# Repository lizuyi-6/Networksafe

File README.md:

# AetherGuard

AetherGuard is a server security platform with a control plane, distributed host agents, a Rust fastpath sidecar, and hardware-backed safety gates for dangerous operations.

Product claim: **AetherGuard 完全最后防线**. Engineering definition: Final Defense Mode is a detectable, auditable, fail-closed mode where the control plane can request and audit dangerous actions, but the final grant is enforced by hardware. The root-resistant variant moves that final network release decision outside the protected server into the self-developed **AetherGuard Root-Resistant Gateway Appliance** — an industrial multi-port gateway appliance integrating an independent security authorization controller, Secure Element / TPM, and hardware-level fail-closed interlock.

## Quick Start

One-shot setup — generates `.env` (Docker) and `backend/.env` (local dev) from the `.env.example` templates with cryptographically random secrets. Existing files are never overwritten:

```bash
node scripts/setup.mjs              # add --install to also npm-install backend/ + frontend/
                                    # bash-only alternative: bash deployment/production/setup-env.sh
```

Docker, all services (requires Docker Compose v2.24+; the legacy `docker-compose` v1 binary cannot parse this compose file):

```bash
node scripts/setup.mjs
docker compose up -d --build

# Console + API proxy: http://127.0.0.1:8080
# Backend/Redis/Postgres/MinIO are internal-only in production Compose.
# Login: ADMIN_EMAIL / ADMIN_PASSWORD from .env — setup prints the generated password once
```

Fresh Linux host, one command (installs Docker if missing, generates `.env`, builds and starts, waits for backend health):

```bash
sudo bash scripts/install.sh
```

Air-gapped customer host (no internet, optionally no preinstalled Docker): build a self-contained bundle on a connected machine, transfer it, install fully offline — details in `deployment/offline/README.md`:

```bash
node scripts/release/build-offline-bundle.mjs --include-docker    # online build machine
# transfer dist/offline/aetherguard-offline-<ver>-<arch>.tar.gz to the customer host, then:
tar -xzf aetherguard-offline-*.tar.gz -C /opt/aetherguard
cd /opt/aetherguard && sudo bash install.sh
```

Local development — the backend refuses to start without `JWT_SECRET` and `AUDIT_LOG_SECRET`, so create `backend/.env` first (the setup script writes it with dev-safe defaults, including `DISABLE_REDIS=true`, which is dev-only and rejected in production):

```bash
node scripts/setup.mjs

cd backend
npm install
npm run dev

cd frontend
npm install
npm run dev
```

Optional components: `simulator/` and `e2e/` are separate npm packages (`node scripts/setup.mjs --all` installs them too); `rust-fastpath/` needs Rust 1.85 (`cargo build --release`); firmware host-side tests need gcc (`make -f test/Makefile test` from `firmware/controller-stm32h5/`).

Release-relevant checks:

```bash
cd backend && npm run typecheck
cd frontend && npm run typecheck
node scripts/guards/check-route-db-access.mjs
node scripts/guards/check-no-direct-api-fetch.mjs
```

## Current Software Validation

The latest software-only local validation is recorded in:

- `docs/reports/software-validation-status-2026-07-27.md`
- `docs/reports/software-validation-status-2026-07-27.json`
- `backend/test-data/dataset-eval-report.json`

Current evidence on the tested x86_64 Linux host:

- Backend: 248 Jest suites and 3,291 tests passed. Coverage is 65.90% statements, 51.41% branches, 65.90% functions, and 66.21% lines. Tests ran with Redis disabled and do not substitute for live external-service integration.
- Synthetic dataset: 4,500 samples produced 63.97% attack detection and 0% false positives on the 1,200 tracked synthetic normal samples. These are corpus results, not production detection or FPR claims.
- Rust fastpath: tests, Clippy, and release build passed. The latest fixed-key loopback reproduction measured 56.6k–61.6k QPS across three rounds, with a short concurrency-sweep peak of 75.1k QPS and no request errors. A stable 100k QPS result was not reproduced in this run.
- Chromium release subset: all 10 runnable tests passed, and 1 pitch-enabled-only test was skipped. This covers the local Chromium release subset only, not every E2E file, browser, operating system, or production deployment.
- Rescue and gateway simulator fail-closed checks passed as software tests only; they do not validate physical hardware.
- Local AI latency, live PostgreSQL/Redis/S3/IdP/notification integrations, ARM64/cross-OS support, agent resource targets, and production network capacity remain unvalidated in this environment.

The historical March 2026 Docker report remains useful as a dated snapshot, but it is not the source of truth for current software performance or dataset claims.

Focused Final Defense checks:

```bash
cd backend
npx jest src/__tests__/services/final-defense.service.test.ts
npx jest src/__tests__/services/hardware-authorization.service.test.ts
npx jest src/__tests__/services/deployment-run.service.test.ts
npx jest src/__tests__/services/device-control.service.test.ts
npx jest src/__tests__/companion/serial-device-companion.test.ts
```

## Architecture

```mermaid
flowchart LR
    User["Operator / API Client"] --> Frontend["React Console"]
    Frontend --> Backend["Node.js Control Plane"]
    Backend --> DB["SQLite / PostgreSQL"]
    Backend --> Redis["Redis"]
    Backend --> Agent["Host Agent"]
    Agent --> Fastpath["Rust Fastpath"]
    Agent --> Companion["Local Companion"]
    Companion --> Board["Gateway Appliance Controller"]
    Board --> Interlock["Hardware Fail-closed Interlock"]
    Agent --> ServerNIC["Server Network Ports"]
    ServerNIC --> NIGW["Gateway Appliance (L2 Bridge)"]
    NIGW --> Network["LAN / WAN"]
    NIGW --> Mgmt["Independent MGMT / Cellular"]
```

Primary components:

| Path | Purpose |
| --- | --- |
| `backend/` | Express API, Socket.IO gateways, services, repositories, companion logic, tests |
| `frontend/` | React console, typed API client, pages, demo data |
| `rust-fastpath/` | High-throughput traffic processing sidecar |
| `e2e/` | Playwright release and UI verification |
| `deployment/` | Production helper scripts and deploy bundles |
| `hardware/aetherguard-network-isolation-gateway-v1/` | AetherGuard Root-Resistant Gateway Appliance hardware baseline (active primary hardware) |
| `hardware/factory/aetherguard-serial-deployer-ev1/` | Archived — legacy serial deployer factory package |
| `hardware/kicad/esp32-serial-deployer-pcb/` | Archived — KiCad source for the legacy serial deployer PCB |
| `docs/` | Architecture, product, readiness, and archive index documents |

## Final Defense Mode

Final Defense Mode treats the backend, database, and API request as potentially untrusted for high-risk actions.

High-risk actions such as `host_remove`, `wipe_data`, `factory_reset`, `recovery_flash`, and `critical_config_change` must satisfy all of the following:

- The local companion reads a signed local policy from `/etc/aetherguard/final-defense-policy.json`.
- The requested action, target, script path, release window, and interlock target are in the local policy allow-list.
- The hardware grant signature verifies against the provisioned hardware public key.
- The grant message includes and matches `policyDigest`, `challenge`, `breakerTarget`, `interlockAction`, payload hash, expiry, and monotonic counter.
- Interlock feedback is healthy and matches the expected state.

Interlock states are normalized as:

```ts
type InterlockState = 'isolated' | 'armed' | 'released' | 'fault' | 'disabled' | 'unknown';
```

Legacy `asserted` is mapped to `isolated`.

Failure behavior is closed by default: signature failure, counter rollback, policy digest mismatch, expired grant, missing external DC, feedback mismatch, board disconnect, or heartbeat loss keeps or returns the management link to `isolated`.

The external product statement is conditional. “完全最后防线” is only valid when the management link is actually wired through the interlock, Final Defense Mode is enabled, the local policy is signed, the secure element is provisioned, and companion plus board health are confirmed. v1 controls the low-voltage network or management link only; it does not switch mains power or directly cut production host power.

## Root-Resistant Final Defense

> **Evidence status (2026-08 security audit): EXPERIMENTAL.** The canonical
> `deployment/gateway` data plane has not passed Linux namespace/L2-bridge
> integration gates, systemd-VM gates, or hardware-in-the-loop campaigns.
> Gateway status is a three-level evidence model — `reported` (self-report),
> `verified` (reserved: signed control-channel verification), `attested`
> (reserved: server-verified hardware attestation quote). Only `attested`
> can drive "Root-Resistant Active"; the attestation verifier is **not yet
> implemented**, so high-risk root-resistant actions stay fail-closed and
> self-reported fields can never restore `active`. See
> `docs/security-audit/2026-08-remediation-matrix.md`.

Root-resistant mode assumes the protected server OS, local agent, local companion, scripts, and host logs may be fully controlled by an attacker with root. In that threat model, the trusted boundary is no longer the host companion. It is the **AetherGuard Root-Resistant Gateway Appliance**:

- Dual 1GbE RJ45 transparent L2 bridge with `SERVER`, `LAN/WAN`, and independent `MGMT` ports; cellular is an optional management path.
- The `SERVER` to `LAN/WAN` bridge is fail-closed. `isolated` blocks protected server forwarding while preserving the gateway's own management channel.
- The appliance holds signed policy state, hardware identity, firmware measurement, and secure-element backed release grants outside the protected server.
- Strong “root-resistant active” status requires the appliance present, policy digest match, firmware digest plus attestation, secure element, both data ports linked, independent management path, and a healthy `armed` or `isolated` bridge state.
- The claim only covers network links physically cabled through the appliance. Out-of-band BMC, Wi-Fi, spare NICs, local console, direct storage damage, and host disk encryption by root are outside v1 protection unless separately controlled.

## Hardware Shapes

| Hardware | Status | Role |
| --- | --- | --- |
| AetherGuard Root-Resistant Gateway Appliance | **Active — primary hardware** | Self-developed industrial multi-port gateway appliance: dual 1GbE transparent L2 bridge (SERVER, LAN/WAN) + independent MGMT port, STM32H5/U5 security authorization controller, Secure Element / TPM (OPTIGA Trust M / SE050 / ATECC608B), hardware-level fail-closed interlock with feedback verification. Controls protected server network release outside the host. |
| Legacy ESP32 serial deployment dongle | Archived (superseded) | Former physical confirmation device for local deployment/removal over USB-TTL serial. Replaced by Gateway Appliance. |
| Legacy Control Board v1 | Archived (superseded) | Former ESP32-S3 + ATECC608C control board for hardware grants. Replaced by Gateway Appliance Controller. |

Gateway Appliance controller protocol is newline-delimited JSON:

- Companion to controller: `hello`, `command physical_confirmation_required`, `command interlock_assert`, `command interlock_release`
- Controller to companion: `state`, `heartbeat`, `alert`, `physical_confirmation_ack`, `interlock_result`

The legacy ESP32 deployment dongle protocol (`AG:REQ:*` allow-list) is archived and no longer active.

## API Surface

Final Defense API routes:

- `GET /api/final-defense/status`
- `POST /api/final-defense/policies`
- `POST /api/final-defense/actions`
- `POST /api/final-defense/gateways/status/report`
- `POST /api/final-defense/gateways/actions`

Route handlers must use `sendSuccess()` and `sendError()` from `backend/src/core/http/api-response.ts`. Route files under `backend/src/api/routes/` must not access the database directly; use services or repositories.

Frontend API calls must go through `frontend/src/services/api.ts`.

## Validation Status

Validated in the current production baseline:

- Backend and frontend typechecks for the Final Defense implementation.
- Route DB access guard.
- Frontend direct API fetch guard.
- Focused Jest coverage for hardware grant signing, Final Defense service policy checks, companion denial of untrusted scripts, deployment run, and device control paths.
- UI status model for root-resistant “Final Defense Active” only when an external AetherGuard Root-Resistant Gateway Appliance reports secure element, matching policy digest, firmware attestation, linked data ports, independent management path, and healthy bridge state. As of the 2026-08 audit this status additionally requires the server-side `attested` verification level, which is not yet reachable — see the Root-Resistant evidence-status note above.

Not yet validated in this workspace:

- Real Gateway Appliance hardware-in-the-loop release and feedback test.
- Secure element provisioning ceremony on physical OPTIGA Trust M / ATECC608B.
- Real Gateway Appliance hardware-in-the-loop bridge isolation and release test.
- Secure boot / measured boot chain for physical gateway firmware.

## Production Rules

- Do not call `ensureSchema()` in request handlers or WebSocket processors. Prepare service-owned tables in `backend/src/bootstrap/persistence.ts`.
- `DB_MODE=postgres` is required for production.
- `DISABLE_REDIS` must not be enabled in production.
- Do not commit generated outputs, KiCad scratch trees, router exchange files, probe reports, or generated PPTX decks.
- Demo and pitch-only frontend routes such as `/aetherguard-deck` are disabled by default. Set `VITE_ENABLE_PITCH_ROUTES=true` only for local demo builds.

## Artifact Archive

Large generated artifacts and hardware experiment intermediates were moved out of the repository to:

```text
X:\repos\Networksafe-archive\20260513-pre-cleanup
```

See `docs/artifact-archive-index.md` for the archive categories and file-level manifest location.

## License

MIT. See `LICENSE`.

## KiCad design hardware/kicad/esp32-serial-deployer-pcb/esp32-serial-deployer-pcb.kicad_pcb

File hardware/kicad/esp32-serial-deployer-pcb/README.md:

# ESP32 Serial Deployer PCB v1

This directory contains the first single-board KiCad project for the ESP32 serial deployer.

## Scope

- Board size: `100 mm x 72 mm`
- Stack-up: `4-layer`, `1.6 mm FR-4`
- Mounting: `4 x M2` holes, `3.5 mm` inset from each edge
- Architecture:
  - `ESP32-WROOM-32E`
  - `CP2102N` service/debug bridge on rear `USB-C`
  - `CP2102N` host bridge on right-side `USB-A` pigtail pads
  - Dual `VBUS` inputs ORed into `5V_SYS`
  - `AP2112K-3.3` main regulator
  - On-board OLED header, three UI buttons, RGB LED, buzzer driver, BOOT/RESET, test points

## Files

- `esp32-serial-deployer-pcb.kicad_pro`
- `esp32-serial-deployer-pcb.kicad_sch`
- `esp32-serial-deployer-pcb.kicad_pcb`
- `esp32-serial-deployer-pcb.kicad_sym`
- `esp32-serial-deployer-pcb.pretty/`
- `fp-lib-table`
- `sym-lib-table`
- `reports/`
- `tools/generate_pcb_v1.py`
- `tools/repair_pcb_connectivity.py`

## Source Of Truth

- The KiCad project files in this directory are the active design source.
- `tools/generate_pcb_v1.py` is now a reference/base-board generator used to keep symbol, footprint, and net assignments synchronized.
- Recovery experiments live in `scratch/` and are not the fabrication source of truth.

## Interface Baseline

- OLED: `GPIO21` / `GPIO22`
- Buttons: `GPIO18` / `GPIO19` / `GPIO23`
- RGB: `GPIO25` / `GPIO26` / `GPIO27`
- Buzzer driver: `GPIO14`
- Host deployment UART: `GPIO16` / `GPIO17`
- Service/debug UART: `GPIO1` / `GPIO3`

## Power Strategy

- `USB-C VBUS -> PTC fuse -> Schottky OR -> 5V_SYS`
- `Host pigtail VBUS -> PTC fuse -> Schottky OR -> 5V_SYS`
- `5V_SYS -> AP2112K-3.3 -> 3V3`
- Both `CP2102N` bridges are modeled as `3V3`-powered devices with their respective USB `VBUS` pins sensed through divider networks.

## USB Split

- Rear `USB-C`: flashing, debug console, service power input
- Right-side `USB-A` pigtail: target-host deployment bridge only
- The two USB data paths are electrically separate

## BOM Direction

Use JLC/LCSC-friendly packages wherever possible:

- QFN-24 `CP2102N`
- `ESP32-WROOM-32E`
- `AP2112K-3.3` in `SOT-23-5`
- `0603` passives
- `SOD-123` Schottky diodes
- Small `SOT-23` NPNs for auto-download and buzzer drive

## KiCad 9 Status

The project now loads in `KiCad 9.0.7` CLI:

- `kicad-cli sch export netlist` succeeds
- `kicad-cli sch erc` runs and writes `reports/erc.rpt`
- `kicad-cli pcb drc` runs and writes `reports/drc.rpt`
- `kicad-cli pcb drc --schematic-parity` runs and writes `reports/parity.rpt`

Current validation is not yet clean and the board is not fabrication-ready:

- ERC: currently high-noise and still requires schematic cleanup
- PCB DRC: stable board baseline is down to `3` DRC violations plus `39` unconnected items
- The remaining PCB issues are concentrated in explicit ground/power closure, not broad project load failures
- Schematic parity still needs cleanup after the exposed-pad and ground-net corrections

This means the project is a KiCad 9 native, editable recovery baseline, but it is not ready for fabrication yet. The remaining work is board-quality cleanup:

- finish the remaining ground and power routing closure
- clean up ERC and schematic-parity drift introduced during recovery
- verify footprint drill sizes and custom footprints against final purchased parts
- re-run DRC/DRC parity after the next routing pass

## Firmware Profile

Use the new PlatformIO environment `serial_deployer_pcb_v1` for the PCB variant. It keeps the same GPIO map and switches `BUZZER_ACTIVE_LEVEL` to `HIGH`.

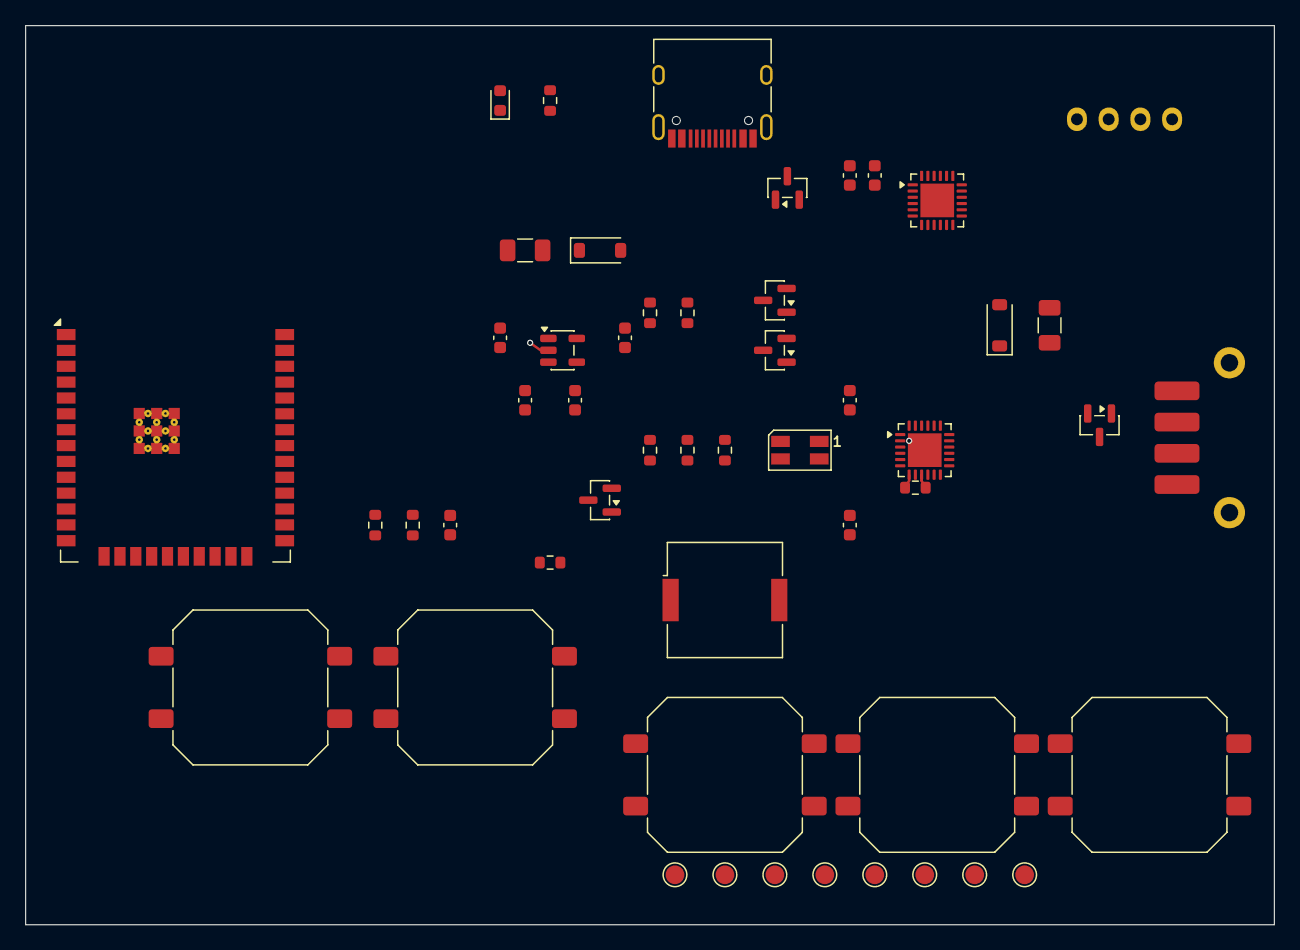
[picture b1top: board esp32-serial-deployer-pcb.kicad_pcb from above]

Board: 4 copper layers, 100.0 x 72.0 mm, 51 parts (0 on the bottom side), 37 nets.

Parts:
BZ1: Buzzer; Buzzer_Murata_PKMCS0909E
C1, C2, C9: 10u; C_0603_1608Metric
C3: 1u; C_0603_1608Metric
C4, C6, C8: 0.1u; C_0603_1608Metric
C5, C7: 4.7u; C_0603_1608Metric
D1, D2: B5819W; D_SOD-123
D3: PWR LED; LED_0603_1608Metric
D10: RGB LED; LED_RGB_Wuerth-PLCC4_3.2x2.8mm_150141M173100
F1, F2: PTC500mA; Fuse_1206_3216Metric
J1: Service USB-C; USB_C_Receptacle_HRO_TYPE-C-31-M-12
J2: USB-A Pigtail; USB_A_Pigtail_Pads_1x4_Edge
J3: OLED 0.96in I2C; OLED_096_I2C_Module_1x4
Q1, Q2, Q3: MMBT3904; SOT-23
R1, R2: 5.1k; R_0603_1608Metric
R3, R4: 10k; R_0603_1608Metric
R13, R14, R15: 330; R_0603_1608Metric
R16, R18: 1k; R_0603_1608Metric
R17: 4.7k; R_0603_1608Metric
SW1: BOOT; SW_Push_1P1T_NO_CK_PTS125Sx43SMTR
SW2: RESET; SW_Push_1P1T_NO_CK_PTS125Sx43SMTR
SW3: OK; SW_Push_1P1T_NO_CK_PTS125Sx43SMTR
SW4: NEXT; SW_Push_1P1T_NO_CK_PTS125Sx43SMTR
SW5: BACK; SW_Push_1P1T_NO_CK_PTS125Sx43SMTR
TP1: 3V3; TestPoint_Pad_D1.5mm
TP2: GND; TestPoint_Pad_D1.5mm
TP3: EN; TestPoint_Pad_D1.5mm
TP4: IO0; TestPoint_Pad_D1.5mm
TP5: TX0; TestPoint_Pad_D1.5mm
TP6: RX0; TestPoint_Pad_D1.5mm
TP7: TX2; TestPoint_Pad_D1.5mm
TP8: RX2; TestPoint_Pad_D1.5mm
U1: ESP32-WROOM-32E
U2: CP2102N Service; QFN-24-1EP_4x4mm_P0.5mm_EP2.7x2.7mm
U3: CP2102N Host; QFN-24-1EP_4x4mm_P0.5mm_EP2.7x2.7mm
U4: AP2112K-3.3; SOT-23-5
U5, U6: USB ESD; SOT-23

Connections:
3V3: BZ1.1, C2.1, C4.1, C5.1, C6.1, C7.1, C8.1, C9.1, J3.1, R3.1, R4.1, R16.1, R18.1, TP1.1, U1.2, U2.5, U2.6, U2.7, U2.9, U3.5, U3.6, U3.7, U4.5
5V_SYS: C1.1, D1.2, D2.2, U4.1, U4.3
BTN_BACK: SW5.1, U1.37
BTN_NEXT: SW4.1, U1.31
BTN_OK: SW3.1, U1.30
BUZZER_CTRL: R17.1, U1.13
BUZZER_CTRL_DRV: Q3.1, R17.2
BUZZER_SW: BZ1.2, Q3.3
ESP_EN: C3.1, Q1.3, R3.2, SW2.1, TP3.1, U1.3
ESP_IO0: Q2.3, R4.2, SW1.1, TP4.1, U1.25
GND: C1.2, C2.2, C3.2, C4.2, C5.2, C6.2, C7.2, C8.2, C9.2, D3.1, D10.2, J1.A1, J1.A12, J1.B1, J1.B12, J1.S1, J2.4, J3.2, Q1.2, Q2.2, Q3.2, R1.2, R2.2, SW1.2, SW2.2, SW3.2, SW4.2, SW5.2, TP2.1, U1.1, U1.39, U2.2, U2.25, U3.2, U3.25, U4.2, U5.2, U6.2
HOST_CP2102_RST_N: R18.2, U3.9
HOST_DN: J2.2, U3.4, U6.3
HOST_DP: J2.3, U3.3, U6.1
LED_B: D10.4, R15.1
LED_B_DRV: R15.2, U1.12
LED_G: D10.3, R14.1
LED_G_DRV: R14.2, U1.11
LED_R: D10.1, R13.1
LED_R_DRV: R13.2, U1.10
OLED_SCL: J3.3, U1.36
OLED_SDA: J3.4, U1.33
PWR_LED_N: D3.2, R16.2
UART0_RX: TP6.1, U1.34, U2.20
UART0_TX: TP5.1, U1.35, U2.21
UART2_RX: TP8.1, U1.27, U3.20
UART2_TX: TP7.1, U1.28, U3.21
USB_CC1: J1.A5, R1.1
USB_CC2: J1.B5, R2.1
USB_C_DN: J1.A7, J1.B7, U2.4, U5.3
USB_C_DP: J1.A6, J1.B6, U2.3, U5.1
USB_DTR: Q2.1, U2.23
USB_RTS: Q1.1, U2.19
VBUS_HOST_PROT: D2.1, F2.2
VBUS_HOST_RAW: F2.1, J2.1, U3.8
VBUS_USB_C_PROT: D1.1, F1.2
VBUS_USB_C_RAW: F1.1, J1.A4, J1.A9, J1.B4, J1.B9, U2.8

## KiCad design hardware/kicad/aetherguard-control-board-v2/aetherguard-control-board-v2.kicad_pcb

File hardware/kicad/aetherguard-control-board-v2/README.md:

# AetherGuard Control Board v2 KiCad Project

Single-host physical authorization board with RTC, SD card audit logging, and Wi-Fi/BLE.

## Changes from v1

- Added PCF8563 RTC with CR1220 battery backup (I2C 0x51, shared bus)
- Added Micro-SD card slot (SPI mode, GPIO1/2/3/6)
- Expanded ESP32-S3 symbol to expose GPIO1-3, 6-7
- Added 2x 47uF bulk capacitors on 3.3V rail for peak current headroom
- Wi-Fi/BLE enabled (ESP32-S3 PCB antenna, keepout zone preserved)

## Board Specs

- 90mm x 60mm, 4-layer FR-4, 1.6mm
- ENIG surface finish, black solder mask
- JLCPCB SMT compatible (0603 passives, LCSC parts)

## Schematic Hierarchy (5 sheets)

1. `sheets/power-input.kicad_sch` — USB-C, ESD, TPS2121, LMR16006, AP2112K
2. `sheets/mcu-usb-secure.kicad_sch` — ESP32-S3, ATECC608C, USB, UART
3. `sheets/ui-panel.kicad_sch` — OLED, RGB LED, buttons, buzzer
4. `sheets/isolated-io.kicad_sch` — Optocoupler interlock I/O
5. `sheets/rtc-storage.kicad_sch` — PCF8563 RTC + CR1220 + Micro-SD

## Key Components

| Ref | Part | Package | LCSC | Function |
|-----|------|---------|------|----------|
| U1 | ESP32-S3-WROOM-1-N8R2 | Module | — | Main MCU |
| U2 | ATECC608C-SSHDA-T | SOIC-8 | C649795 | Secure element |
| U3 | LMR16006YDDCR | SOT-23-6 | C477878 | 12/24V→5V buck |
| U4 | AP2112K-3.3TRG1 | SOT-23-5 | C51118 | 5V→3.3V LDO |
| U5 | TPS2121DRLR | DHWQFN-14 | C477879 | Power OR-ing |
| U7,U8 | VOS617A | SO-4 | C131455 | Optocouplers |
| U9 | PCF8563T/5 | SOIC-8 | C7488 | RTC |
| BT1 | CR1220 holder | SMD | C70377 | RTC battery |
| J1 | USB4110-GF-A | USB-C | — | USB connector |
| J6 | TF-115 | SMD | C393941 | Micro-SD slot |

## GPIO Assignment

| GPIO | Function | Sheet |
|------|----------|-------|
| 0 | BOOT | mcu-usb-secure |
| 1 | SD_MOSI | rtc-storage |
| 2 | SD_MISO | rtc-storage |
| 3 | SD_SCK | rtc-storage |
| 4 | Cancel button | ui-panel |
| 5 | Confirm button | ui-panel |
| 6 | SD_CS | rtc-storage |
| 7 | RTC_INT# | rtc-storage |
| 8 | I2C SDA | mcu-usb-secure |
| 9 | I2C SCL | mcu-usb-secure |
| 10 | ATECC wake | mcu-usb-secure |
| 11 | RGB LED R | ui-panel |
| 12 | RGB LED G | ui-panel |
| 13 | RGB LED B | ui-panel |
| 14 | Buzzer PWM | ui-panel |
| 15 | Interlock OUT | isolated-io |
| 16 | Interlock FB | isolated-io |
| 17 | UART TX | mcu-usb-secure |
| 18 | UART RX | mcu-usb-secure |
| 19 | USB D- | mcu-usb-secure |
| 20 | USB D+ | mcu-usb-secure |
| 21 | Ext power sense | power-input |

## Layer Stack

| Layer | Function |
|-------|----------|
| F.Cu | Signal + components |
| In1.Cu | Solid GND plane |
| In2.Cu | Power (5V/3.3V split) + signal |
| B.Cu | Signal + components |

## Validation

```powershell
$cli = 'C:\Program Files\KiCad\9.0\bin\kicad-cli.exe'
$tmp = Join-Path $env:TEMP 'ag-v2-test'
New-Item -ItemType Directory -Force -Path $tmp | Out-Null

& $cli sch erc hardware/kicad/aetherguard-control-board-v2/aetherguard-control-board-v2.kicad_sch --output "$tmp\erc.rpt"
& $cli pcb drc hardware/kicad/aetherguard-control-board-v2/aetherguard-control-board-v2.kicad_pcb --output "$tmp\drc.rpt"
```

## Manufacturing Target

JLCPCB 4-layer prototype:
- FR-4, 1.6mm, 1oz copper
- ENIG or HASL lead-free
- Black solder mask, white silkscreen
- Min trace/space: 0.15mm
- Signal via: 0.3/0.6mm drill/pad
- Power via: 0.5/1.0mm drill/pad

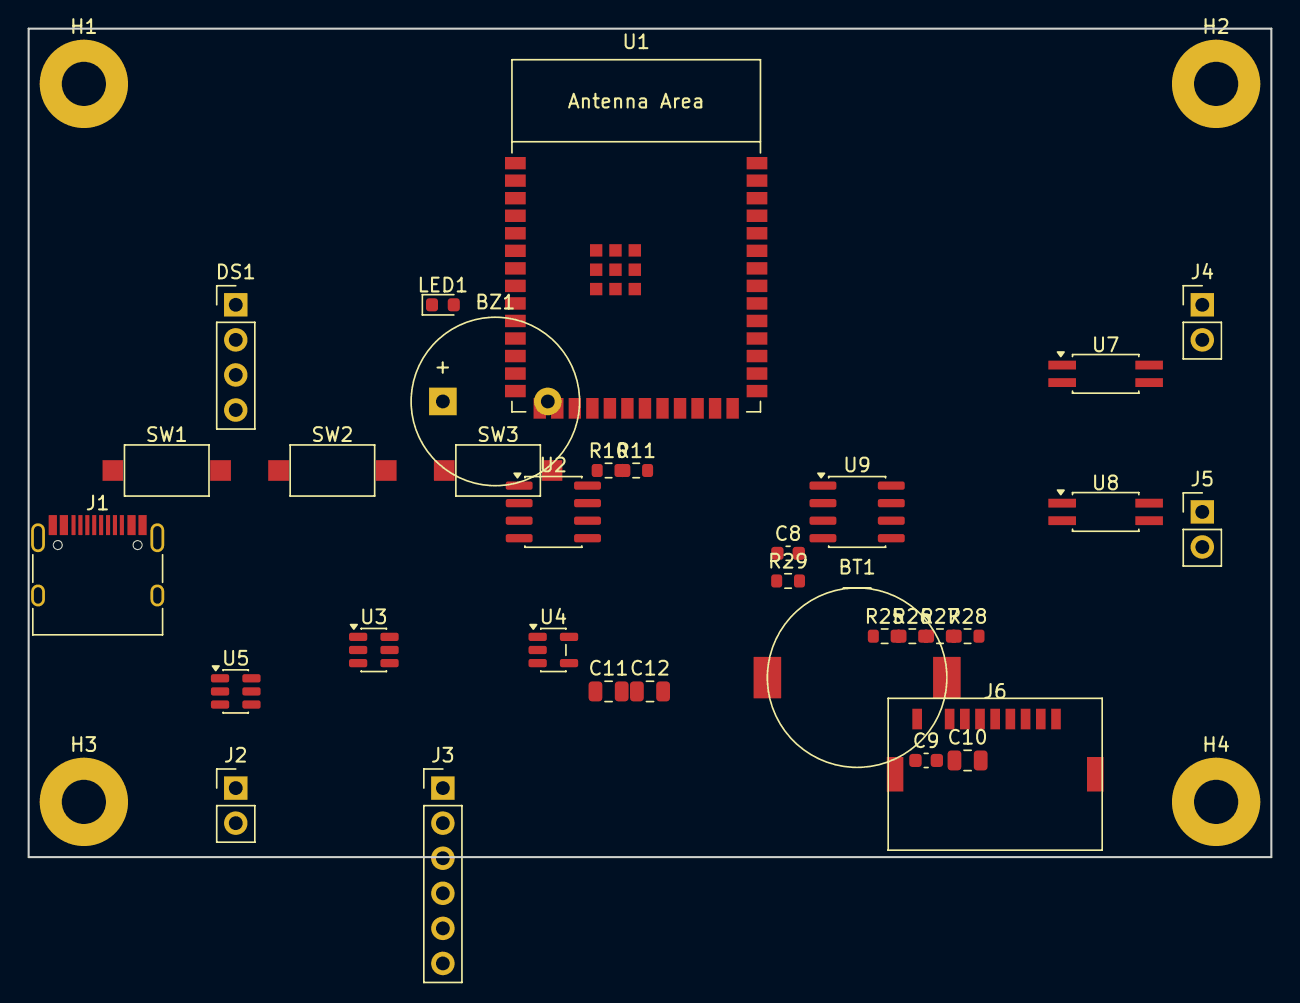
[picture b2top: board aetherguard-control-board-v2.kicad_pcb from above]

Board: 4 copper layers, 90.0 x 60.0 mm, 37 parts (0 on the bottom side), 5 nets, no tracks yet.

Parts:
BT1: CR1220; AetherGuard_CR1220_Holder
BZ1: Buzzer_12x9.5RM7.6
C8, C9: C_0603_1608Metric
C10, C11, C12: C_0805_2012Metric
DS1: PinHeader_1x04_P2.54mm_Vertical
H1, H2, H3, H4: MountingHole_3.2mm_M3_Pad
J1: AetherGuard_USB4110_GFA
J2, J4, J5: PinHeader_1x02_P2.54mm_Vertical
J3: PinHeader_1x06_P2.54mm_Vertical
J6: Micro_SD; AetherGuard_MicroSD_Push_Push
LED1: LED_0603_1608Metric
R10, R11, R25, R26, R27, R28, R29: R_0603_1608Metric
SW1, SW2, SW3: SW_SPST_CK_RS282G05A3
U1: AetherGuard_ESP32-S3-WROOM-1
U2, U9: SOIC-8_3.9x4.9mm_P1.27mm
U3, U5: SOT-23-6
U4: SOT-23-5
U7, U8: SO-4_4.4x2.3mm_P1.27mm

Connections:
5V_SYS: U4.1, U5.2
+3V3: BT1.1, C8.1, C9.1, C10.1, C11.1, C12.1, DS1.2, R10.1, R11.1, R25.1, R26.1, R27.1, R28.1, R29.1, U2.8, U4.5, U9.8
GND: BT1.2, C8.2, C9.2, C10.2, C11.2, C12.2, DS1.1, H1.1, H2.1, H3.1, H4.1, J2.2, U2.4, U3.5, U4.2, U5.5, U7.3, U8.3, U9.4
I2C_SCL: DS1.3, R11.2, U2.6, U9.6
I2C_SDA: DS1.4, R10.2, U2.5, U9.5

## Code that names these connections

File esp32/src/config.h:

/**
 * AetherGuard ESP32 serial deployer configuration.
 *
 * Default baseline:
 * - Jumper prototype on an ESP32 development board
 * - 0.96" I2C OLED
 * - Three buttons wired to GND with INPUT_PULLUP
 * - Common-cathode RGB module
 * - Active-low buzzer module
 * - One external CP2102 used in deployment mode on UART2
 *
 * Optional board profile:
 * - AG_HW_PROFILE_PCB_V1=1 for the single-board KiCad PCB variant
 * - Keeps the same GPIO map, but flips the buzzer control polarity to HIGH
 */

#ifndef CONFIG_H
#define CONFIG_H

#include <Arduino.h>

// Feature flags
#ifndef ENABLE_ENCRYPTION
#define ENABLE_ENCRYPTION       0
#endif

#ifndef ENABLE_EXPERIMENTAL_CLOUD
#define ENABLE_EXPERIMENTAL_CLOUD 0
#endif

#ifndef AG_HW_PROFILE_PCB_V1
#define AG_HW_PROFILE_PCB_V1     0
#endif

// 1. I2C OLED (SSD1306)
#define ENABLE_SCREEN           1
#define SCREEN_WIDTH            128
#define SCREEN_HEIGHT           64
#define SCREEN_ADDRESS          0x3C
#define DISPLAY_I2C_CLOCK_HZ    400000
#define PIN_I2C_SDA             21
#define PIN_I2C_SCL             22

// 2. Buttons
// Use non-strap GPIOs so a held button does not disturb boot.
#define PIN_BTN_OK              18
#define PIN_BTN_NEXT            19
#define PIN_BTN_BACK            23

// 3. RGB module
#define PIN_RGB_RED             25
#define PIN_RGB_GREEN           26
#define PIN_RGB_BLUE            27
#define RGB_COMMON_ANODE        0

// 4. Buzzer module
#define PIN_BUZZER              14
#define BUZZER_ACTIVE           1
#if AG_HW_PROFILE_PCB_V1
#define BUZZER_ACTIVE_LEVEL     HIGH
#else
#define BUZZER_ACTIVE_LEVEL     LOW
#endif

// 5. Target-host serial link (deployment mode via external CP2102)
#define TARGET_SERIAL           Serial2
#define TARGET_RX_PIN           16
#define TARGET_TX_PIN           17
#define TARGET_BAUD             115200

// Deployment protocol
#define SERIAL_REQ_ENV               "AG:REQ:ENV"
#define SERIAL_REQ_BACKUP            "AG:REQ:BACKUP"
#define SERIAL_REQ_INSTALL           "AG:REQ:INSTALL"
#define SERIAL_REQ_REMOVE            "AG:REQ:REMOVE"

// Operator-facing helper status messages
#define HOST_HELPER_NOT_READY_MSG    "Host helper not ready"
#define HOST_HELPER_TIMEOUT_MSG      "Timeout waiting for host helper"

// Serial protocol markers
#define SERIAL_PROTO_ENV_LINUX       "AG:ENV:LINUX"
#define SERIAL_PROTO_ENV_WINDOWS     "AG:ENV:WINDOWS"
#define SERIAL_PROTO_BEGIN_PREFIX    "AG:BEGIN:"
#define SERIAL_PROTO_STEP_PREFIX     "AG:STEP:"
#define SERIAL_PROTO_OK_PREFIX       "AG:OK:"
#define SERIAL_PROTO_ERR_PREFIX      "AG:ERR:"
#define SERIAL_PROTO_OK_BACKUP       "AG:OK:BACKUP"
#define SERIAL_PROTO_ERR_BACKUP      "AG:ERR:BACKUP"
#define SERIAL_PROTO_OK_INSTALL      "AG:OK:INSTALL"
#define SERIAL_PROTO_ERR_INSTALL     "AG:ERR:INSTALL"
#define SERIAL_PROTO_OK_REMOVE       "AG:OK:REMOVE"
#define SERIAL_PROTO_ERR_REMOVE      "AG:ERR:REMOVE"

// Buffers
#define RX_BUFFER_SIZE           2048
#define SERIAL_LINE_BUFFER_SIZE  128
#define JSON_BUFFER_SIZE         1024
#define TX_BUFFER_SIZE           1024

// Timing
#define ENV_CHECK_TIMEOUT_MS     1500
#define BACKUP_TIMEOUT_MS        15000
#define INSTALL_TIMEOUT_MS       45000
#define REMOVE_TIMEOUT_MS        20000
#define BOOT_SPLASH_MS           900
#define UI_SPINNER_INTERVAL_MS   250
#define LOOP_IDLE_DELAY_MS       1

// --- Deploy Bundle (SPIFFS cache for offline deployment) ---
#define DEPLOY_BUNDLE_MAX_SIZE    (1024 * 1024)     // 1 MB max bundle
#define RECEIVE_CHUNK_SIZE       1024               // Each chunk during USB write
#define DEPLOY_FILE_NAME_MAX     64                 // Max filename length
#define SPIFFS_MOUNT_POINT       "/deploy"           // SPIFFS mount point
#define SPIFFS_MAX_FILES         10
#define SPIFFS_MAX_FILE_SIZE     (512 * 1024)        // 512 KB per file
#define DEPLOY_WRITE_TIMEOUT_MS  30000               // 30s to receive full bundle
#define DEPLOY_PLAY_TIMEOUT_MS   60000               // 60s to play bundle to target

// WiFi / WebSocket / local control plane defaults
// NOTE: The current v1 target is the USB-TTL serial deployer. Cloud-device
// modules remain experimental and are not part of the active build target.
#define WIFI_SSID                "AetherGuard-Setup"
#define WIFI_PASSWORD            "aetherguard123"
#define LOCAL_HOST               "192.168.4.1"
#define LOCAL_PORT               8080
#define SERVER_HOST              "192.168.4.1"
#define SERVER_PORT              3005
#define SERVER_PATH              "/ws/status"
#define SERVER_USE_SSL           0
#define WIFI_CONNECT_TIMEOUT     15000

// Device identity defaults
#define DEVICE_ID                "ESP32-001"
#define DEVICE_VERSION           "1.0.0"
#define API_KEY                  "demo-device-key"

// Legacy aliases used by collector/transport modules
#define SERIAL_RX_PIN            TARGET_RX_PIN
#define SERIAL_TX_PIN            TARGET_TX_PIN

// Debug output
#ifndef ENABLE_DEBUG
#define ENABLE_DEBUG             1
#endif

#if ENABLE_DEBUG
    #define DEBUG_PRINT(x)       Serial.print(x)
    #define DEBUG_PRINTLN(x)     Serial.println(x)
    #define DEBUG_PRINTF(...)    Serial.printf(__VA_ARGS__)
#else
    #define DEBUG_PRINT(x)       ((void)0)
    #define DEBUG_PRINTLN(x)     ((void)0)
    #define DEBUG_PRINTF(...)    ((void)0)
#endif

#endif // CONFIG_H

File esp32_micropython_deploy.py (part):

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MAX_RETRY = 3            # 最大重试次数

# 引脚定义
PIN_OLED_SDA = 21
PIN_OLED_SCL = 22
PIN_LED_R = 16
PIN_LED_G = 17
PIN_LED_B = 18
PIN_BTN_ACCEPT = 4
PIN_BTN_ROLLBACK = 5
PIN_BTN_DETAIL = 6
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            return

        # OLED 屏幕
        self.i2c = I2C(scl=Pin(PIN_OLED_SCL), sda=Pin(PIN_OLED_SDA), freq=400000)
        self.oled = ssd1306.SSD1306_I2C(128, 64, self.i2c)
        self.oled_lines = [""] * 6

        # RGB LED
        self.led_r = PWM(Pin(PIN_LED_R), freq=5000, duty=0)
        self.led_g = PWM(Pin(PIN_LED_G), freq=5000, duty=0)
        self.led_b = PWM(Pin(PIN_LED_B), freq=5000, duty=0)
        self.current_color = (0, 0, 0)

        # 按钮
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
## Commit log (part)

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2026-06-12 feat(hardware): add control board v2 KiCad design and gateway-v1 review footprints
    Control Board v2 — single-host physical authorization board with RTC,
    SD-card audit logging, Wi-Fi/BLE (supersedes the archived v1):
    - 5-sheet hierarchical schematic (power-input, mcu-usb-secure,
    ui-panel, isolated-io, rtc-storage)
    - routed + unrouted .kicad_pcb, project, symbol library, lib tables
    - custom footprint library (.pretty)
2026-06-12 test(e2e): add full-flow and security-hardening acceptance specs
    - e2e/tests/acceptance-full-flow.spec.ts: end-to-end acceptance flow
    - e2e/tests/security-hardening-acceptance.spec.ts: hardening acceptance
    - e2e/tests/full-clickthrough.spec.ts: updated walkthrough
    - deployment/production/aetherguard-device-companion.env.example: refresh
    companion env template
